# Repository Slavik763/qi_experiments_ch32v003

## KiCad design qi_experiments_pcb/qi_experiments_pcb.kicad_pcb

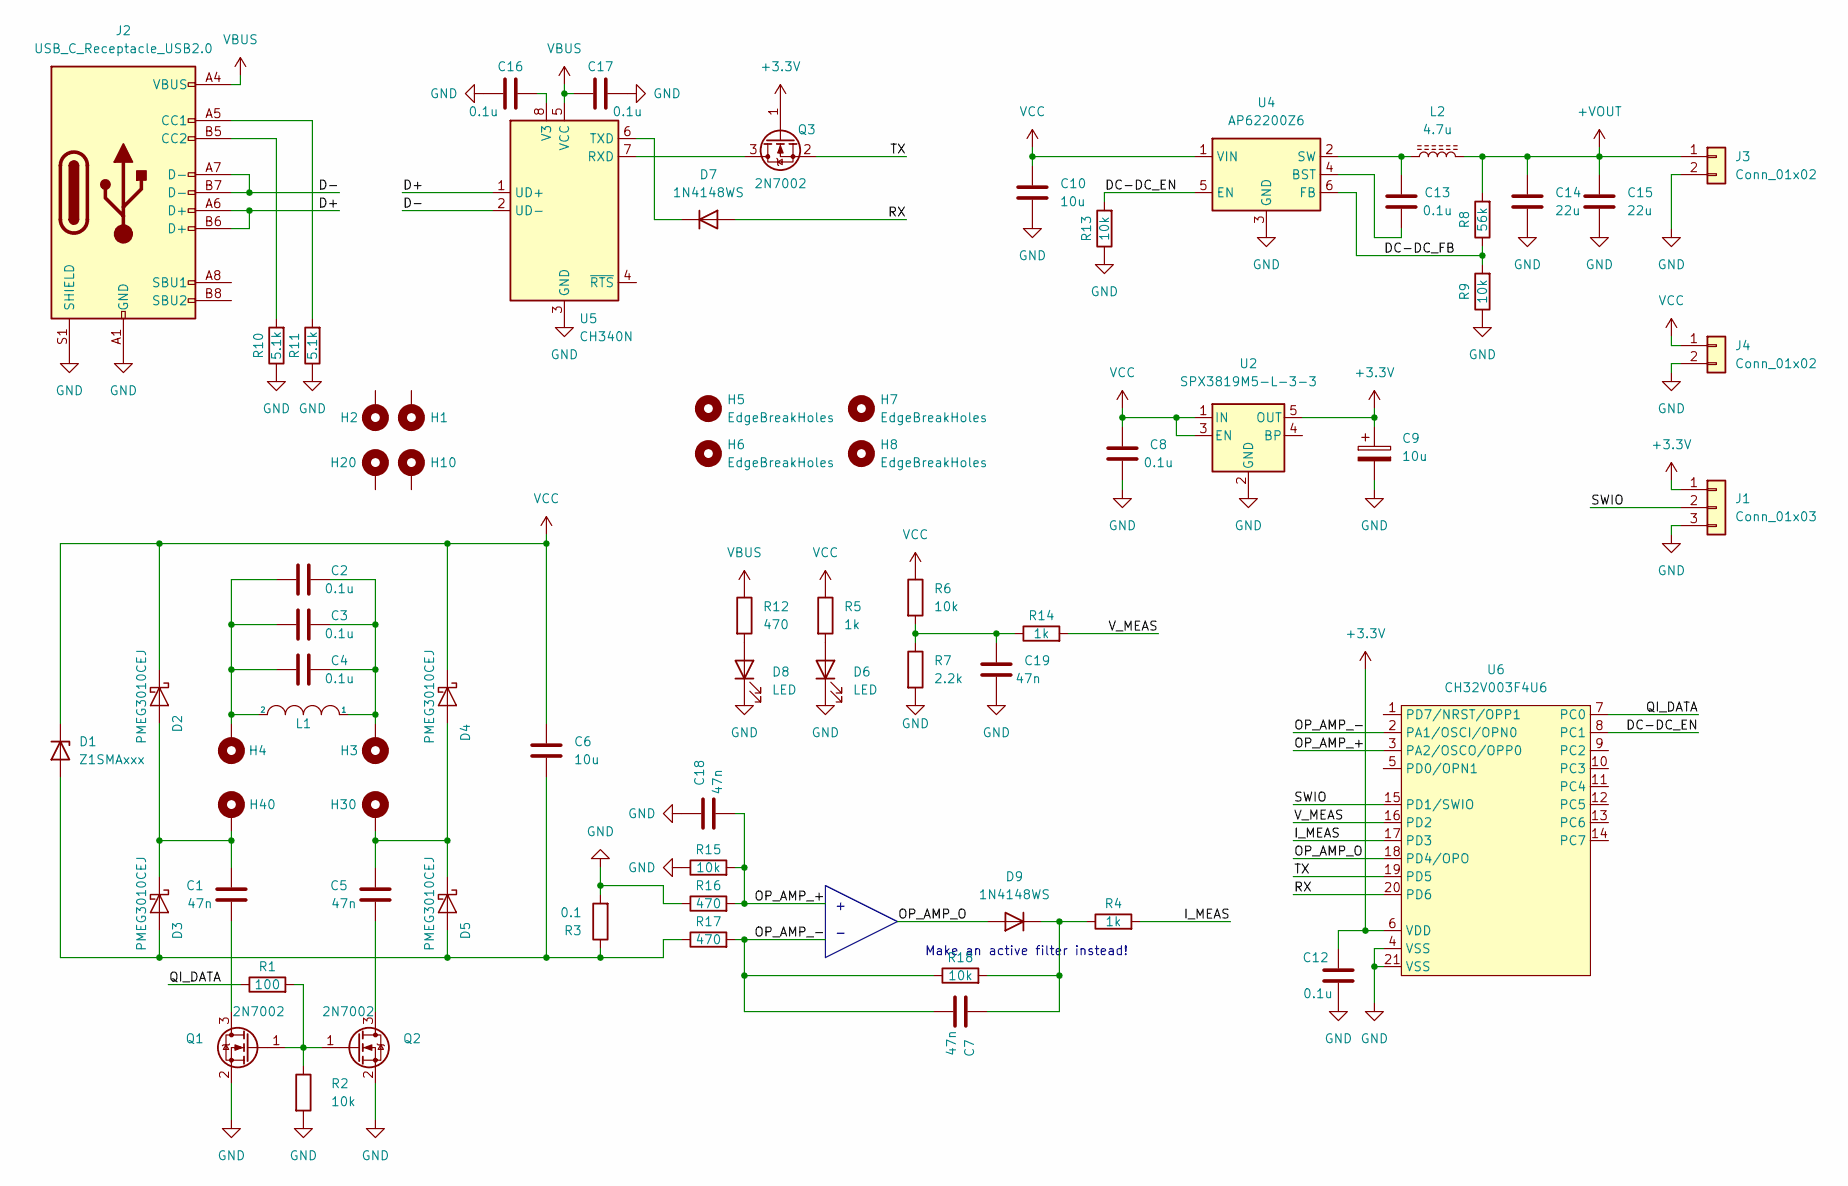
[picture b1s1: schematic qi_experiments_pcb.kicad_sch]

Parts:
C1, C5, C7, C18, C19: 47n; C_0603_1608Metric
C2, C3, C4: 0.1u; C_1206_3216Metric
C6, C10: 10u; C_1206_3216Metric
C8, C12, C13, C16, C17: 0.1u; C_0603_1608Metric
C9: 10u; CP_EIA-3216-18_Kemet-A
C14, C15: 22u; C_1206_3216Metric
D1: Z1SMAxxx; D_SMA
D2, D3, D4, D5: PMEG3010CEJ; D_SOD-323F
D6, D8: LED; LED_0603_1608Metric
D7, D9: 1N4148WS; D_SOD-323
H1, H2, H3, H4, H10, H20, H30, H40: MountingHole_Pad; MountingHole_2.2mm_M2_DIN965_Pad
H5, H6, H7, H8: EdgeBreakHoles; edgeBreakHoles
J1: Conn_01x03; PinHeader_1x03_P2.54mm_Horizontal
J2: USB_C_Receptacle_USB2.0; USB_C_Receptacle_HRO_TYPE-C-31-M-12
J3, J4: Conn_01x02; PinHeader_1x02_P2.54mm_Horizontal
L1: INDUCTOR; pcb_coil_24x24_qi
L2: 4.7u; L_Vishay_IHLP-1616
Q1, Q2, Q3: 2N7002; SOT-23
R1: 100; R_0603_1608Metric
R2, R6, R9, R13, R15, R18: 10k; R_0603_1608Metric
R3: 0.1; R_1206_3216Metric
R4, R5, R14: 1k; R_0603_1608Metric
R7: 2.2k; R_0603_1608Metric
R8: 56k; R_0603_1608Metric
R10, R11: 5.1k; R_0603_1608Metric
R12, R16, R17: 470; R_0603_1608Metric
U2: SPX3819M5-L-3-3; SOT-23-5
U4: AP62200Z6; SOT-563
U5: CH340N; SOIC-8_3.9x4.9mm_P1.27mm
U6: CH32V003F4U6; QFN-20-1EP_3x3mm_P0.4mm_EP1.65x1.65mm

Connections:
+3.3V: C9.1, C12.2, J1.1, Q3.1 (G), U2.5 (OUT), U6.6 (VDD)
+VOUT: C14.1, C15.1, J3.1, L2.2, R8.2
/D+: J2.A6 (D+), J2.B6 (D+), U5.1 (UD+)
/D-: J2.A7 (D-), J2.B7 (D-), U5.2 (UD-)
/DC-DC_EN: R13.2, U4.5 (EN), U6.8 (PC1)
/DC-DC_FB: R8.1, R9.2, U4.6 (FB)
/I_MEAS: R4.2, U6.17 (PD3)
/OP_AMP_+: C18.1, R15.2, R16.2, U6.3 (PA2/OSCO/OPP0)
/OP_AMP_-: C7.1, R17.2, R18.1, U6.2 (PA1/OSCI/OPN0)
/OP_AMP_O: D9.2 (A), U6.18 (PD4/OPO)
/QI_DATA: R1.1, U6.7 (PC0)
/RX: D7.2 (A), U6.20 (PD6)
/SWIO: J1.2, U6.15 (PD1/SWIO)
/TX: Q3.2 (S), U6.19 (PD5)
/V_MEAS: R14.2, U6.16 (PD2)
GND: C8.2, C9.2, C10.2, C12.1, C14.2, C15.2, C16.2, C17.2, C18.2, C19.1, D6.1 (K), D8.1 (K), J1.3, J2.A1 (GND), J2.A12 (GND), J2.B1 (GND), J2.B12 (GND), J2.S1 (SHIELD), J3.2, J4.2, Q1.2 (S), Q2.2 (S), R2.2, R3.2, R7.2, R9.1, R10.1, R11.1, R13.1, R15.1, R16.1, U2.2 (GND), U4.3 (GND), U5.3 (GND), U6.4 (VSS), U6.21 (VSS)
unnamed: C1.1, Q1.3 (D)
unnamed: C1.2, D2.2 (A), D3.1 (K), H40.1
unnamed: C2.1, C3.1, C4.1, H4.1, L1.2
unnamed: C2.2, C3.2, C4.2, H3.1, L1.1
unnamed: C5.1, Q2.3 (D)
unnamed: C5.2, D4.2 (A), D5.1 (K), H30.1
unnamed: C6.2, D1.2 (A), D3.2 (A), D5.2 (A), R3.1, R17.1
unnamed: C7.2, D9.1 (K), R4.1, R18.2
unnamed: C13.1, L2.1, U4.2 (SW)
unnamed: C13.2, U4.4 (BST)
unnamed: C16.1, U5.8 (V3)
unnamed: C19.2, R6.2, R7.1, R14.1
unnamed: D6.2 (A), R5.2
unnamed: D7.1 (K), U5.6 (TXD)
unnamed: D8.2 (A), R12.2
unnamed: J2.A5 (CC1), R11.2
unnamed: J2.B5 (CC2), R10.2
unnamed: Q1.1 (G), Q2.1 (G), R1.2, R2.1
unnamed: Q3.3 (D), U5.7 (RXD)
VBUS: C17.1, J2.A4 (VBUS), J2.A9 (VBUS), J2.B4 (VBUS), J2.B9 (VBUS), R12.1, U5.5 (VCC)
VCC: C6.1, C8.1, C10.1, D1.1 (K), D2.1 (K), D4.1 (K), J4.1, R5.1, R6.1, U2.1 (IN), U2.3 (EN), U4.1 (VIN)

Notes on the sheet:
Make an active filter instead!

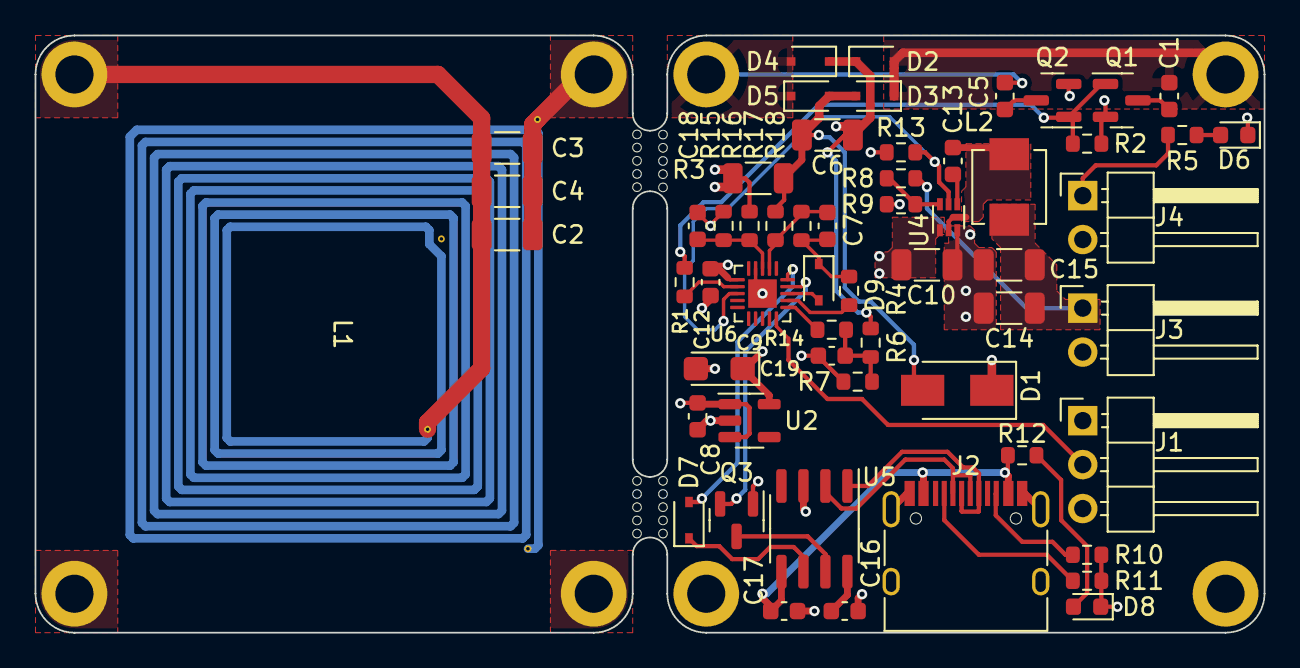
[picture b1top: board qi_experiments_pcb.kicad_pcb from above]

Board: 4 copper layers, 71.0 x 34.5 mm, 70 parts (0 on the bottom side), 37 nets.

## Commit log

2023-04-08 initial: pcb_v1.0_added
2023-06-03 curent sensing amp polarity swap
